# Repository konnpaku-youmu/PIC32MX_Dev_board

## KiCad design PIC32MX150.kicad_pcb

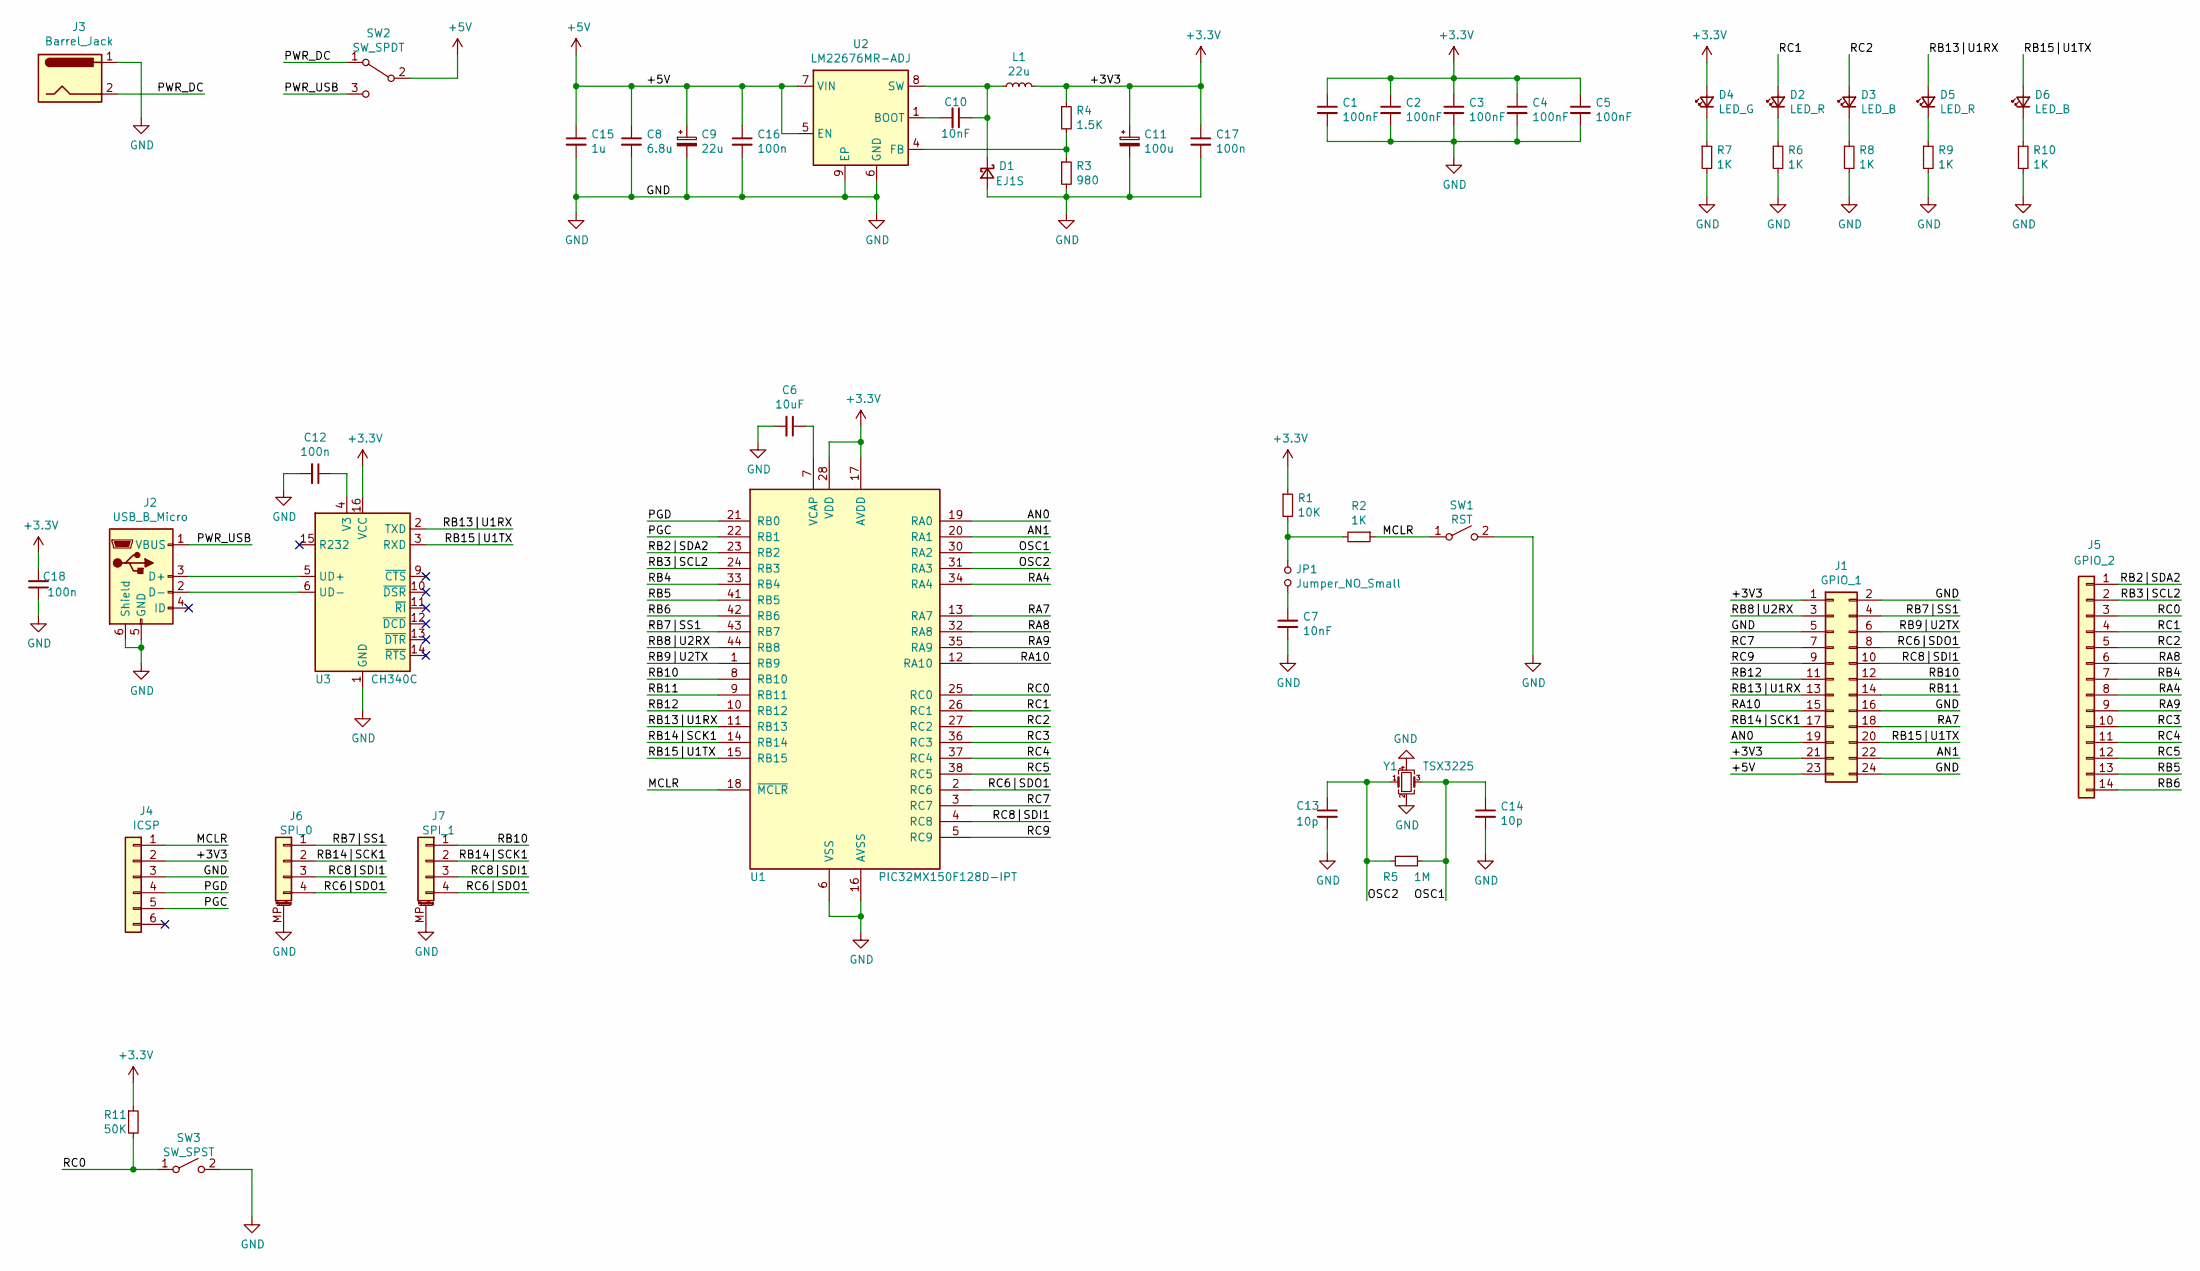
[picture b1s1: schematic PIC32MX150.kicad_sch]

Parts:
C1, C2, C3, C4, C5: 100nF; C_0603_1608Metric_Pad1.08x0.95mm_HandSolder
C6: 10uF; CP_EIA-6032-28_Kemet-C_Pad2.25x2.35mm_HandSolder
C7, C10: 10nF; C_0603_1608Metric_Pad1.08x0.95mm_HandSolder
C8: 6.8u; C_0603_1608Metric_Pad1.08x0.95mm_HandSolder
C9: 22u; CP_Elec_5x5.3
C11: 100u; CP_Elec_5x5.3
C12, C16, C17, C18: 100n; C_0603_1608Metric_Pad1.08x0.95mm_HandSolder
C13, C14: 10p; C_0603_1608Metric_Pad1.08x0.95mm_HandSolder
C15: 1u; C_0603_1608Metric_Pad1.08x0.95mm_HandSolder
D1: EJ1S; D_SOD-123
D2, D5: LED_R; LED_0603_1608Metric_Pad1.05x0.95mm_HandSolder
D3, D6: LED_B; LED_0603_1608Metric_Pad1.05x0.95mm_HandSolder
D4: LED_G; LED_0603_1608Metric_Pad1.05x0.95mm_HandSolder
J1: GPIO_1; PinSocket_2x12_P2.54mm_Vertical
J2: USB_B_Micro; USB_Micro-B_Molex_47346-0001
J3: Barrel_Jack; BarrelJack_Horizontal
J4: ICSP; PinHeader_1x06_P2.54mm_Vertical
J5: GPIO_2; PinHeader_1x14_P2.54mm_Vertical
J6: SPI_0; Molex_PicoBlade_53261-0471_1x04-1MP_P1.25mm_Horizontal
J7: SPI_1; Molex_PicoBlade_53261-0471_1x04-1MP_P1.25mm_Horizontal
JP1: Jumper_NO_Small; SolderJumper-2_P1.3mm_Open_Pad1.0x1.5mm
L1: 22u; L_Sumida_CDMC6D28_7.25x6.5mm
R1: 10K; R_0603_1608Metric_Pad0.98x0.95mm_HandSolder
R2, R6, R7, R8, R9, R10: 1K; R_0603_1608Metric_Pad0.98x0.95mm_HandSolder
R3: 980; R_0603_1608Metric_Pad0.98x0.95mm_HandSolder
R4: 1.5K; R_0603_1608Metric_Pad0.98x0.95mm_HandSolder
R5: 1M; R_0603_1608Metric_Pad0.98x0.95mm_HandSolder
R11: 50K; R_0603_1608Metric_Pad0.98x0.95mm_HandSolder
SW1: RST; SW_SPST_B3U-1000P
SW2: SW_SPDT; SPDT_SW_Big
SW3: SW_SPST; SW_SPST_PTS645
U1: PIC32MX150F128D-IPT; TQFP-44_10x10mm_P0.8mm
U2: LM22676MR-ADJ; TI_SO-PowerPAD-8
U3: CH340C; SOIC-16_3.9x9.9mm_P1.27mm
Y1: TSX3225; Crystal_SMD_SeikoEpson_TSX3225-4Pin_3.2x2.5mm_HandSoldering

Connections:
+3V3: C1.1, C2.1, C3.1, C4.1, C5.1, C11.1, C17.1, C18.2, D4.2 (A), J1.1, J1.21, J4.2, L1.2, R1.1, R4.1, R11.1, U1.17 (AVDD), U1.28 (VDD), U1.40 (VDD), U3.16 (VCC); also elsewhere on the board
+5V: C8.1, C9.1, C15.1, C16.1, J1.23, SW2.2 (B), U2.5 (EN), U2.7 (VIN)
/AN0: J1.19, U1.19 (RA0)
/AN1: J1.22, U1.20 (RA1)
/MCLR: J4.1, R2.1, SW1.1 (A), U1.18 (~MCLR); also elsewhere on the board
/OSC1: C14.1, R5.1, U1.30 (RA2), Y1.3
/OSC2: C13.1, R5.2, U1.31 (RA3), Y1.1
/PGC: J4.5, U1.22 (RB1); also elsewhere on the board
/PGD: J4.4, U1.21 (RB0); also elsewhere on the board
/PWR_DC: J3.2, SW2.1 (A)
/PWR_USB: J2.1 (VBUS), SW2.3 (C)
/RA4: J5.8, U1.34 (RA4)
/RA7: J1.18, U1.13 (RA7)
/RA8: J5.6, U1.32 (RA8)
/RA9: J5.9, U1.35 (RA9)
/RA10: J1.15, U1.12 (RA10)
/RB2|SDA2: J5.1, U1.23 (RB2)
/RB3|SCL2: J5.2, U1.24 (RB3)
/RB4: J5.7, U1.33 (RB4)
/RB5: J5.13, U1.41 (RB5)
/RB6: J5.14, U1.42 (RB6)
/RB7|SS1: J1.4, J6.1, U1.43 (RB7)
/RB8|U2RX: J1.3, U1.44 (RB8)
/RB9|U2TX: J1.6, U1.1 (RB9)
/RB10: J1.12, J7.1, U1.8 (RB10)
/RB11: J1.14, U1.9 (RB11)
/RB12: J1.11, U1.10 (RB12)
/RB13|U1RX: D5.2 (A), J1.13, U1.11 (RB13), U3.2 (TXD)
/RB14|SCK1: J1.17, J6.2, J7.2, U1.14 (RB14)
/RB15|U1TX: D6.2 (A), J1.20, U1.15 (RB15), U3.3 (RXD)
/RC0: J5.3, R11.2, SW3.1 (A), U1.25 (RC0)
/RC1: D2.2 (A), J5.4, U1.26 (RC1)
/RC2: D3.2 (A), J5.5, U1.27 (RC2)
/RC3: J5.10, U1.36 (RC3)
/RC4: J5.11, U1.37 (RC4)
/RC5: J5.12, U1.38 (RC5)
/RC6|SDO1: J1.8, J6.4, J7.4, U1.2 (RC6)
/RC7: J1.7, U1.3 (RC7)
/RC8|SDI1: J1.10, J6.3, J7.3, U1.4 (RC8)
/RC9: J1.9, U1.5 (RC9)
GND: C1.2, C2.2, C3.2, C4.2, C5.2, C6.2, C7.2, C8.2, C9.2, C11.2, C12.2, C13.2, C14.2, C15.2, C16.2, C17.2, C18.1, D1.2 (A), J1.2, J1.5, J1.16, J1.24, J2.5 (GND), J2.6 (Shield), J3.1, J4.3, J6.MP (MountPin), J7.MP (MountPin), R3.2, R6.2, R7.2, R8.2, R9.2, R10.2, SW1.2 (B), SW3.2 (B), U1.6 (VSS), U1.16 (AVSS), U1.29 (VSS), U1.39 (VSS), U2.6 (GND), U2.9 (EP), U3.1 (GND), Y1.2, Y1.4; also elsewhere on the board
unnamed: C6.1, U1.7 (VCAP)
unnamed: C7.1, JP1.2
unnamed: C10.1, D1.1 (K), L1.1, U2.8 (SW)
unnamed: C10.2, U2.1 (BOOT)
unnamed: C12.1, U3.4 (V3)
unnamed: D2.1 (K), R6.1
unnamed: D3.1 (K), R8.1
unnamed: D4.1 (K), R7.1
unnamed: D5.1 (K), R9.1
unnamed: D6.1 (K), R10.1
unnamed: J2.2 (D-), U3.6 (UD-)
unnamed: J2.3 (D+), U3.5 (UD+)
unnamed: JP1.1, R1.2, R2.2
unnamed: R3.1, R4.2, U2.4 (FB)

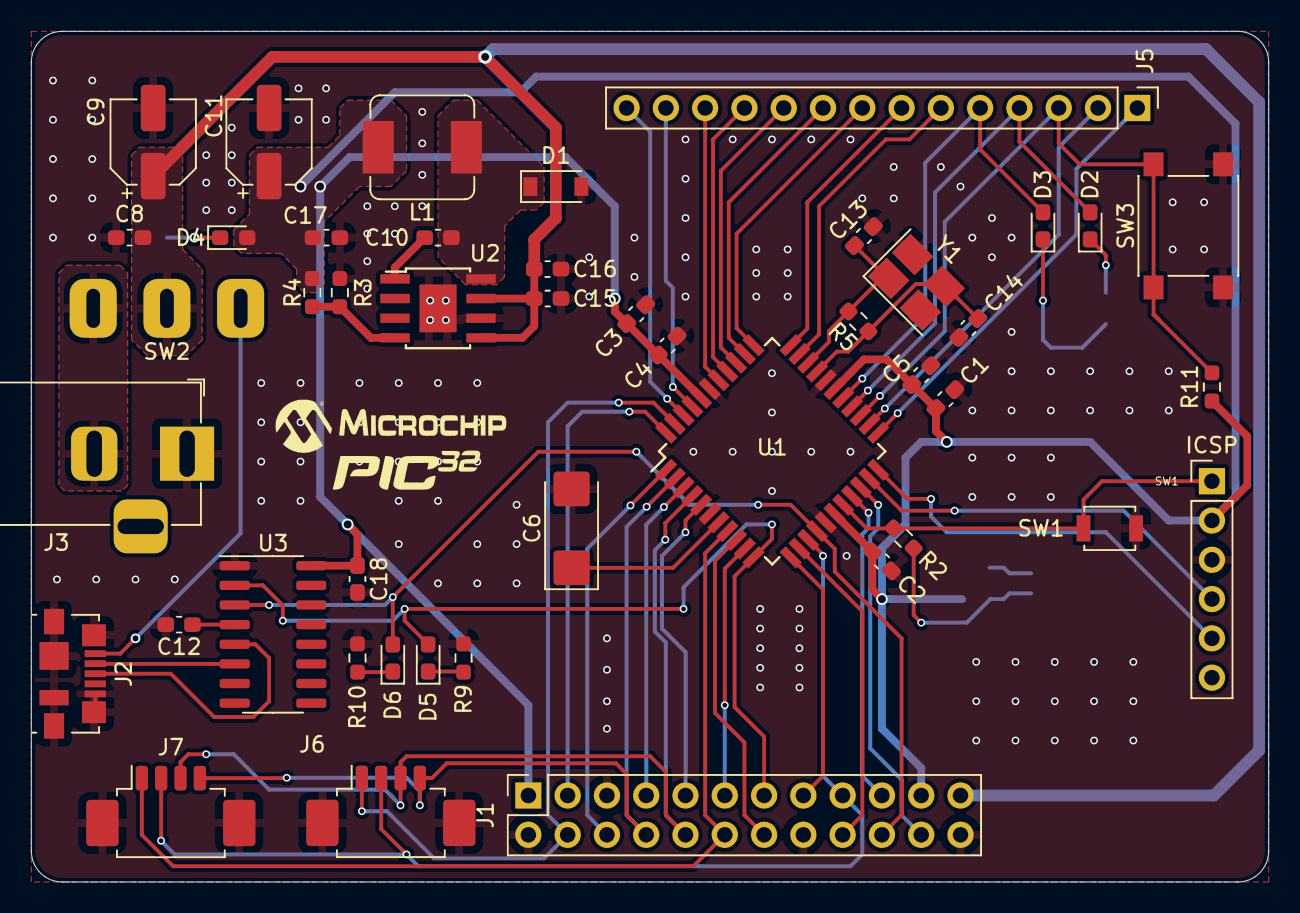
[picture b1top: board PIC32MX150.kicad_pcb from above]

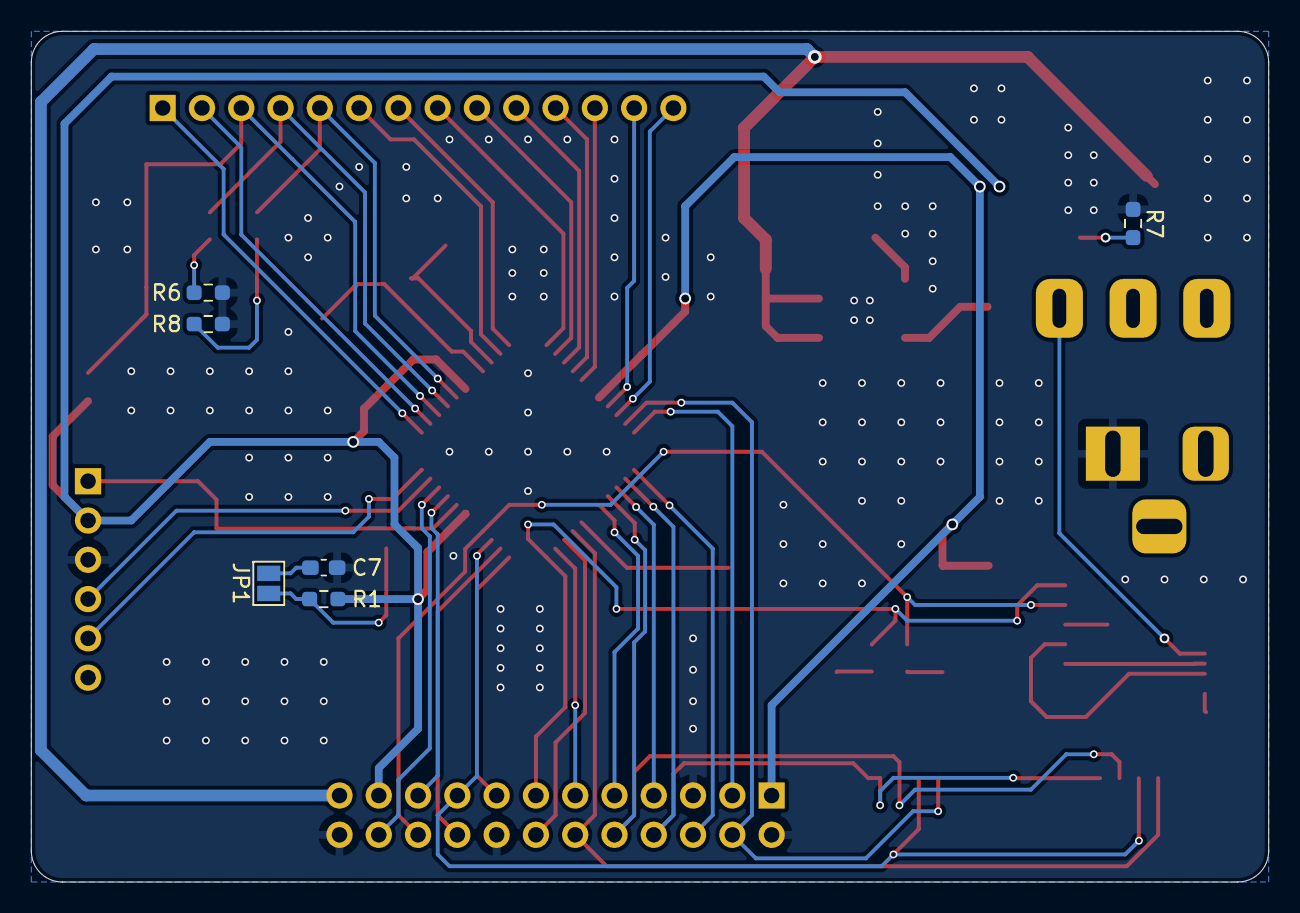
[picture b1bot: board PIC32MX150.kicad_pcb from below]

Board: 2 copper layers, 80.0 x 55.0 mm, 51 parts (6 on the bottom side), 55 nets.

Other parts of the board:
ICSP: ICSP; PinHeader_1x06_P2.54mm_Vertical

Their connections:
+3V3: ICSP.2; also elsewhere on the board
/MCLR: ICSP.1; also elsewhere on the board
/PGC: ICSP.5; also elsewhere on the board
/PGD: ICSP.4; also elsewhere on the board
GND: ICSP.3; also elsewhere on the board

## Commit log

2021-04-20 inductor
2021-04-27 gerber
2021-05-07 LM22676 active-high
